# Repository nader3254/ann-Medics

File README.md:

# Ann-Medics System

This repo is for university graduation project

## What is Ann-Medics ?

Ann-Medics is a enhanced Remote Medical Device that store the 
human vitalities and monitor it for doctors,nurses and other medical stuff ,
it also  management system that works to organize the doctors’ hours, especially the anesthesiologists, given that their number is few in the world. Instead of waiting for the anesthesiologist for the patient to prepare for anesthesia, he can do anything else until this humble system summons him and sends a message to the doctor, and thus we will be as much as possible to save the treating doctor’s time.
 
https://www.youtube.com/watch?v=FgDbxe8dL8w&ab_channel=naderhany

## General setup  
**Host machine:** Ubuntu 18.04.4 LTS or later   
**Target machine:** Raspberry Pi 3B  , AD8232 ecg module , Max30102 ,buzzer 

## Setting up the environment for Raspberry pi
---

1. Download the raspbian image and 
```
  sudo apt install rpi-imager
``` 
note:select any raspbian lite image because we don't 
need to have x11 or wayland gui 

2. install the package dependencies
```
 sudo apt-get install libboost-all-dev libudev-dev libinput-dev libts-dev libmtdev-dev libjpeg-dev libfontconfig1-dev libssl-dev libdbus-1-dev libglib2.0-dev libxkbcommon-dev libegl1-mesa-dev libgbm-dev libgles2-mesa-dev mesa-common-dev libasound2-dev libpulse-dev gstreamer1.0-omx libgstreamer1.0-dev libgstreamer-plugins-base1.0-dev  gstreamer1.0-alsa libvpx-dev libsrtp2-dev libsnappy-dev libnss3-dev "^libxcb.*" flex bison libxslt-dev ruby gperf libbz2-dev libcups2-dev libatkmm-1.6-dev libxi6 libxcomposite1 libfreetype6-dev libicu-dev libsqlite3-dev libxslt1-dev
``` 
``` 
 sudo apt-get install libavcodec-dev libavformat-dev libswscale-dev libx11-dev freetds-dev libsqlite3-dev libpq-dev libiodbc2-dev firebird-dev libgst-dev libxext-dev libxcb1 libxcb1-dev libx11-xcb1 libx11-xcb-dev libxcb-keysyms1 libxcb-keysyms1-dev libxcb-image0 libxcb-image0-dev libxcb-shm0 libxcb-shm0-dev libxcb-icccm4 libxcb-icccm4-dev libxcb-sync1 libxcb-sync-dev libxcb-render-util0 libxcb-render-util0-dev libxcb-xfixes0-dev libxrender-dev libxcb-shape0-dev libxcb-randr0-dev libxcb-glx0-dev libxi-dev libdrm-dev libxcb-xinerama0 libxcb-xinerama0-dev libatspi2.0-dev libxcursor-dev libxcomposite-dev libxdamage-dev libxss-dev libxtst-dev libpci-dev libcap-dev libxrandr-dev libdirectfb-dev libaudio-dev libxkbcommon-x11-dev

``` 
This will install a bunch of libraries from the Debian repository that Qt needed to deploy various kinds of applications on Raspberry Pi.

We also will make a directory that will hold the Qt installation targeting Raspberry Pi, as specified in the previous section. Actually, this can be done at every time before sending Qt 6 build from host machine to the Raspberry Pi, but in this guide we will create it now:
```
 sudo mkdir /usr/local/qt6
```
this is all for raspberry pi

## Setting up the environment for HOST Machine 
---

1. Install Cross Compiler
```
sudo apt install gcc-aarch64-linux-gnu g++-aarch64-linux-gnu
```
2. Setting up SSH Connection

We also want to setup an SSH connection between Raspberry Pi and a host machine. This is needed to transfer data between both devices. The official Raspberry Pi documentation page provided a very detailed and thorough instruction on how to setup SSH between Raspberry Pi and other device, so you can refer this step into that https://www.raspberrypi.com/documentation/computers/remote-access.html#ssh.

3. Building Sysroot from Device

We need to build a Sysroot from our own Raspberry Pi device in the host machine. To do this, we will copy and paste a few directories from Raspberry Pi using rsync through SSH. If rsync is not installed yet in your host machine, simply install it by executing sudo apt install rsync.

After the host machine and Raspberry Pi is connected,
```
 rsync -avz --rsync-path="sudo rsync" --delete <pi_username>@<pi_ip_address>:/lib rpi-sysroot
 rsync -avz --rsync-path="sudo rsync" --delete <pi_username>@<pi_ip_address>:/usr/include rpi-sysroot/usr
 rsync -avz --rsync-path="sudo rsync" --delete <pi_username>@<pi_ip_address>:/usr/lib rpi-sysroot/usr
 rsync -avz --rsync-path="sudo rsync" --delete <pi_username>@<pi_ip_address>:/opt/vc rpi-sysroot/opt
```
Change <pi_username> and <pi_ip_address> with your Raspberry Pi username and IP Address, respectively.

Note: Your Raspberry Pi might not have a directory named /opt/vc, and it is fine. Usually this directory contains proprietary Broadcom libraries, but during the testing the author did not find any issue with the lack of this directory.

After building our own sysroot, we need to fix absolute symbolic links that were broken during the syncing process by converting them to relative symlinks. The easiest, fastest way to do this is to use a command-line tool called symlinks, which is available from the Ubuntu official repository.
```
 sudo apt install symlinks
 cd ~
 symlinks -rc rpi-sysroot
```

---
1. downloading qt source codes 
```
cd $HOME
git clone "https://codereview.qt-project.org/qt/qt5"
cd qt5/
git checkout 6.4.0
perl init-repository -f
cd ..
mkdir $HOME/qt-hostbuild
cd $HOME/qt-hostbuild/
cmake ../qt5/ -GNinja -DCMAKE_BUILD_TYPE=Release -DQT_BUILD_EXAMPLES=OFF -DQT_BUILD_TESTS=OFF -DCMAKE_INSTALL_PREFIX=$HOME/qt-host
cmake --build . --parallel 8
cmake --install .
```

2. Create a Toolchain File

First, we want to create our own CMake toolchain file. This file is important to link the right compilers and libraries so that CMake can produces the suitable Qt build for Raspberry Pi. For this guide, we will use the following CMake code and save it as toolchain.cmake.
```
cmake_minimum_required(VERSION 3.18)
include_guard(GLOBAL)

set(CMAKE_SYSTEM_NAME Linux)
set(CMAKE_SYSTEM_PROCESSOR arm)

set(TARGET_SYSROOT /path/to/your/sysroot)
set(CMAKE_SYSROOT ${TARGET_SYSROOT})

set(ENV{PKG_CONFIG_PATH} $PKG_CONFIG_PATH:/usr/lib/aarch64-linux-gnu/pkgconfig)
set(ENV{PKG_CONFIG_LIBDIR} /usr/lib/pkgconfig:/usr/share/pkgconfig/:${TARGET_SYSROOT}/usr/lib/aarch64-linux-gnu/pkgconfig:${TARGET_SYSROOT}/usr/lib/pkgconfig)
set(ENV{PKG_CONFIG_SYSROOT_DIR} ${CMAKE_SYSROOT})

# if you use other version of gcc and g++ than gcc/g++ 9, you must change the following variables
set(CMAKE_C_COMPILER /usr/bin/aarch64-linux-gnu-gcc-9)
set(CMAKE_CXX_COMPILER /usr/bin/aarch64-linux-gnu-g++-9)

set(CMAKE_C_FLAGS "${CMAKE_C_FLAGS} -I${TARGET_SYSROOT}/usr/include")
set(CMAKE_CXX_FLAGS "${CMAKE_C_FLAGS}")

set(QT_COMPILER_FLAGS "-march=armv8-a")
set(QT_COMPILER_FLAGS_RELEASE "-O2 -pipe")
set(QT_LINKER_FLAGS "-Wl,-O1 -Wl,--hash-style=gnu -Wl,--as-needed")

set(CMAKE_FIND_ROOT_PATH_MODE_PROGRAM NEVER)
set(CMAKE_FIND_ROOT_PATH_MODE_LIBRARY ONLY)
set(CMAKE_FIND_ROOT_PATH_MODE_INCLUDE ONLY)
set(CMAKE_FIND_ROOT_PATH_MODE_PACKAGE ONLY)
set(CMAKE_INSTALL_RPATH_USE_LINK_PATH TRUE)
set(CMAKE_BUILD_RPATH ${TARGET_SYSROOT})

include(CMakeInitializeConfigs)

function(cmake_initialize_per_config_variable _PREFIX _DOCSTRING)
  if (_PREFIX MATCHES "CMAKE_(C|CXX|ASM)_FLAGS")
    set(CMAKE_${CMAKE_MATCH_1}_FLAGS_INIT "${QT_COMPILER_FLAGS}")
        
    foreach (config DEBUG RELEASE MINSIZEREL RELWITHDEBINFO)
      if (DEFINED QT_COMPILER_FLAGS_${config})
        set(CMAKE_${CMAKE_MATCH_1}_FLAGS_${config}_INIT "${QT_COMPILER_FLAGS_${config}}")
      endif()
    endforeach()
  endif()

  if (_PREFIX MATCHES "CMAKE_(SHARED|MODULE|EXE)_LINKER_FLAGS")
    foreach (config SHARED MODULE EXE)
      set(CMAKE_${config}_LINKER_FLAGS_INIT "${QT_LINKER_FLAGS}")
    endforeach()
  endif()

  _cmake_initialize_per_config_variable(${ARGV})
endfunction()

set(XCB_PATH_VARIABLE ${TARGET_SYSROOT})

set(GL_INC_DIR ${TARGET_SYSROOT}/usr/include)
set(GL_LIB_DIR ${TARGET_SYSROOT}:${TARGET_SYSROOT}/usr/lib/aarch64-linux-gnu/:${TARGET_SYSROOT}/usr:${TARGET_SYSROOT}/usr/lib)

set(EGL_INCLUDE_DIR ${GL_INC_DIR})
set(EGL_LIBRARY ${XCB_PATH_VARIABLE}/usr/lib/aarch64-linux-gnu/libEGL.so)

set(OPENGL_INCLUDE_DIR ${GL_INC_DIR})
set(OPENGL_opengl_LIBRARY ${XCB_PATH_VARIABLE}/usr/lib/aarch64-linux-gnu/libOpenGL.so)

set(GLESv2_INCLUDE_DIR ${GL_INC_DIR})
set(GLIB_LIBRARY ${XCB_PATH_VARIABLE}/usr/lib/aarch64-linux-gnu/libGLESv2.so)

set(GLESv2_INCLUDE_DIR ${GL_INC_DIR})
set(GLESv2_LIBRARY ${XCB_PATH_VARIABLE}/usr/lib/aarch64-linux-gnu/libGLESv2.so)

set(gbm_INCLUDE_DIR ${GL_INC_DIR})
set(gbm_LIBRARY ${XCB_PATH_VARIABLE}/usr/lib/aarch64-linux-gnu/libgbm.so)

set(Libdrm_INCLUDE_DIR ${GL_INC_DIR})
set(Libdrm_LIBRARY ${XCB_PATH_VARIABLE}/usr/lib/aarch64-linux-gnu/libdrm.so)

set(XCB_XCB_INCLUDE_DIR ${GL_INC_DIR})
set(XCB_XCB_LIBRARY ${XCB_PATH_VARIABLE}/usr/lib/aarch64-linux-gnu/libxcb.so)
```
Now that we have our toolchain, as well as the cross compiler and sysroot, we can continue with configuring and building Qt for our Raspberry Pi!

As decided in the planning process, we will put all build configuration files on qtpi-build, so let's cd into that directory:
```
 cd ~/qtpi-build
```
Now inside this directory, we can run this configuration command:
```
 ../qt5/configure -release -opengl es2 -nomake examples -nomake tests -qt-host-path $HOME/qt-host -extprefix $HOME/qt-raspi -prefix /usr/local/qt6 -device linux-rasp-pi4-aarch64 -device-option CROSS_COMPILE=aarch64-linux-gnu- -- -DCMAKE_TOOLCHAIN_FILE=$HOME/toolchain.cmake -DQT_FEATURE_xcb=ON -DFEATURE_xcb_xlib=ON -DQT_FEATURE_xlib=ON
The command above will run a configuration script that came with the Qt source code and complementing it with the CMake toolchain that we just created. It is equivalent to this CMake command:
```
```
 cmake ../qt5/ -GNinja -DCMAKE_BUILD_TYPE=Release -DINPUT_opengl=es2 -DQT_BUILD_EXAMPLES=OFF -DQT_BUILD_TESTS=OFF -DQT_HOST_PATH=$HOME/qt-host -DCMAKE_STAGING_PREFIX=$HOME/qt-raspi -DCMAKE_INSTALL_PREFIX=/usr/local/qt6 -DCMAKE_TOOLCHAIN_FILE=$HOME/toolchain.cmake -DQT_QMAKE_TARGET_MKSPEC=devices/linux-rasp-pi4-aarch64 -DQT_FEATURE_xcb=ON -DFEATURE_xcb_xlib=ON -DQT_FEATURE_xlib=ON
```
Note: Both commands will do exactly the same thing: configuring Qt to be installed in folder qt-raspi on the host machine, with expectation that it will populate usr/local/qt6 on the Raspberry Pi. If you already run the first command, then there is no need to run the second command.

The Qt installation from this build will be suitable to run Qt ARM64 applications using X11 as the windowing system. You can check this page from Qt Docs to learn more about xcb plugins.

In more advanced cases, check this page from Qt Documentation if you want to use other windowing systems such as Wayland or EGLFS.

We can then proceed with building and installing.
```
 cmake --build . --parallel 4
 cmake --install .
```
After Qt is successfully installed on ~/qt-raspi, we will then send this Qt installation back to the Raspberry Pi.

To do this, we can use rsync as we did when building sysroot, or scp. Both will accomplish the same thing, and there should be no significant difference between both of them.

To use rsync:
```
rsync -avz --rsync-path="sudo rsync" /path/to/qt-raspi/* <pi_username>@<pi_ip_address>:/usr/local/qt6
```
To use scp:
```
 cd ~/qt-raspi
 scp -r * <pi_username>@<pi_ip_address>:/usr/local/qt6
```

3. Final Configuration on Raspberry Pi
To ensure our Qt 5 installation can be run on Raspberry Pi, we need to setup a few environment variables. All of this can be done on the host device via SSH.
```
ssh pi@169.254.187.77
```
## enter your raspberry pi user password, if prompted
```
 export LD_LIBRARY_PATH=$LD_LIBRARY_PATH:/usr/local/qt6/lib/
```

4. Compiling and Running Qt Project
```
 cd ~/qt5/qtbase/examples/gui/analogclock/
 ls ## make sure there is a CMakeLists.txt file
 ~/qt-raspi/bin/qt-cmake CMakeLists.txt
```
### CMake is configuring here. After it is done without any error, we can proceed to build and install it
```
 cmake --build . --parallel 4
 cmake --install .
```
We now have the binary of our application ready to be run on the Raspberry Pi. We can then send the binary to our Raspberry Pi using either scp or rsync and run the application (either through SSH or directly on the Raspberry Pi with keyboard and mouse connected).
```
 scp -r gui_analogclock <pi_username>@<pi_ip_address>:/home/pi
 ssh <pi_username>@<pi_ip_address>
 cd ~ ## or cd to the directory where you send the binary
 ./gui_analogclock
```

now you are ready download our repo and go to device directory and build it
for your device .

# References 

1. [Qt Documentation](https://doc.qt.io/qt-5/index.html)  
2. [Using Qt Creator to cross-compile and debug Raspberry Pi Qt5 apps ](https://jumpnowtek.com/rpi/Qt-Creator-Setup-for-RPi-cross-development.html) 
3. [Qt C++ GUI Tutorial for Beginners](https://www.youtube.com/playlist?list=PLS1QulWo1RIZiBcTr5urECberTITj7gjA)  
4. [Intel Edison audio output to Bluetooth speaker](https://tl00.wordpress.com/2015/01/28/11/)

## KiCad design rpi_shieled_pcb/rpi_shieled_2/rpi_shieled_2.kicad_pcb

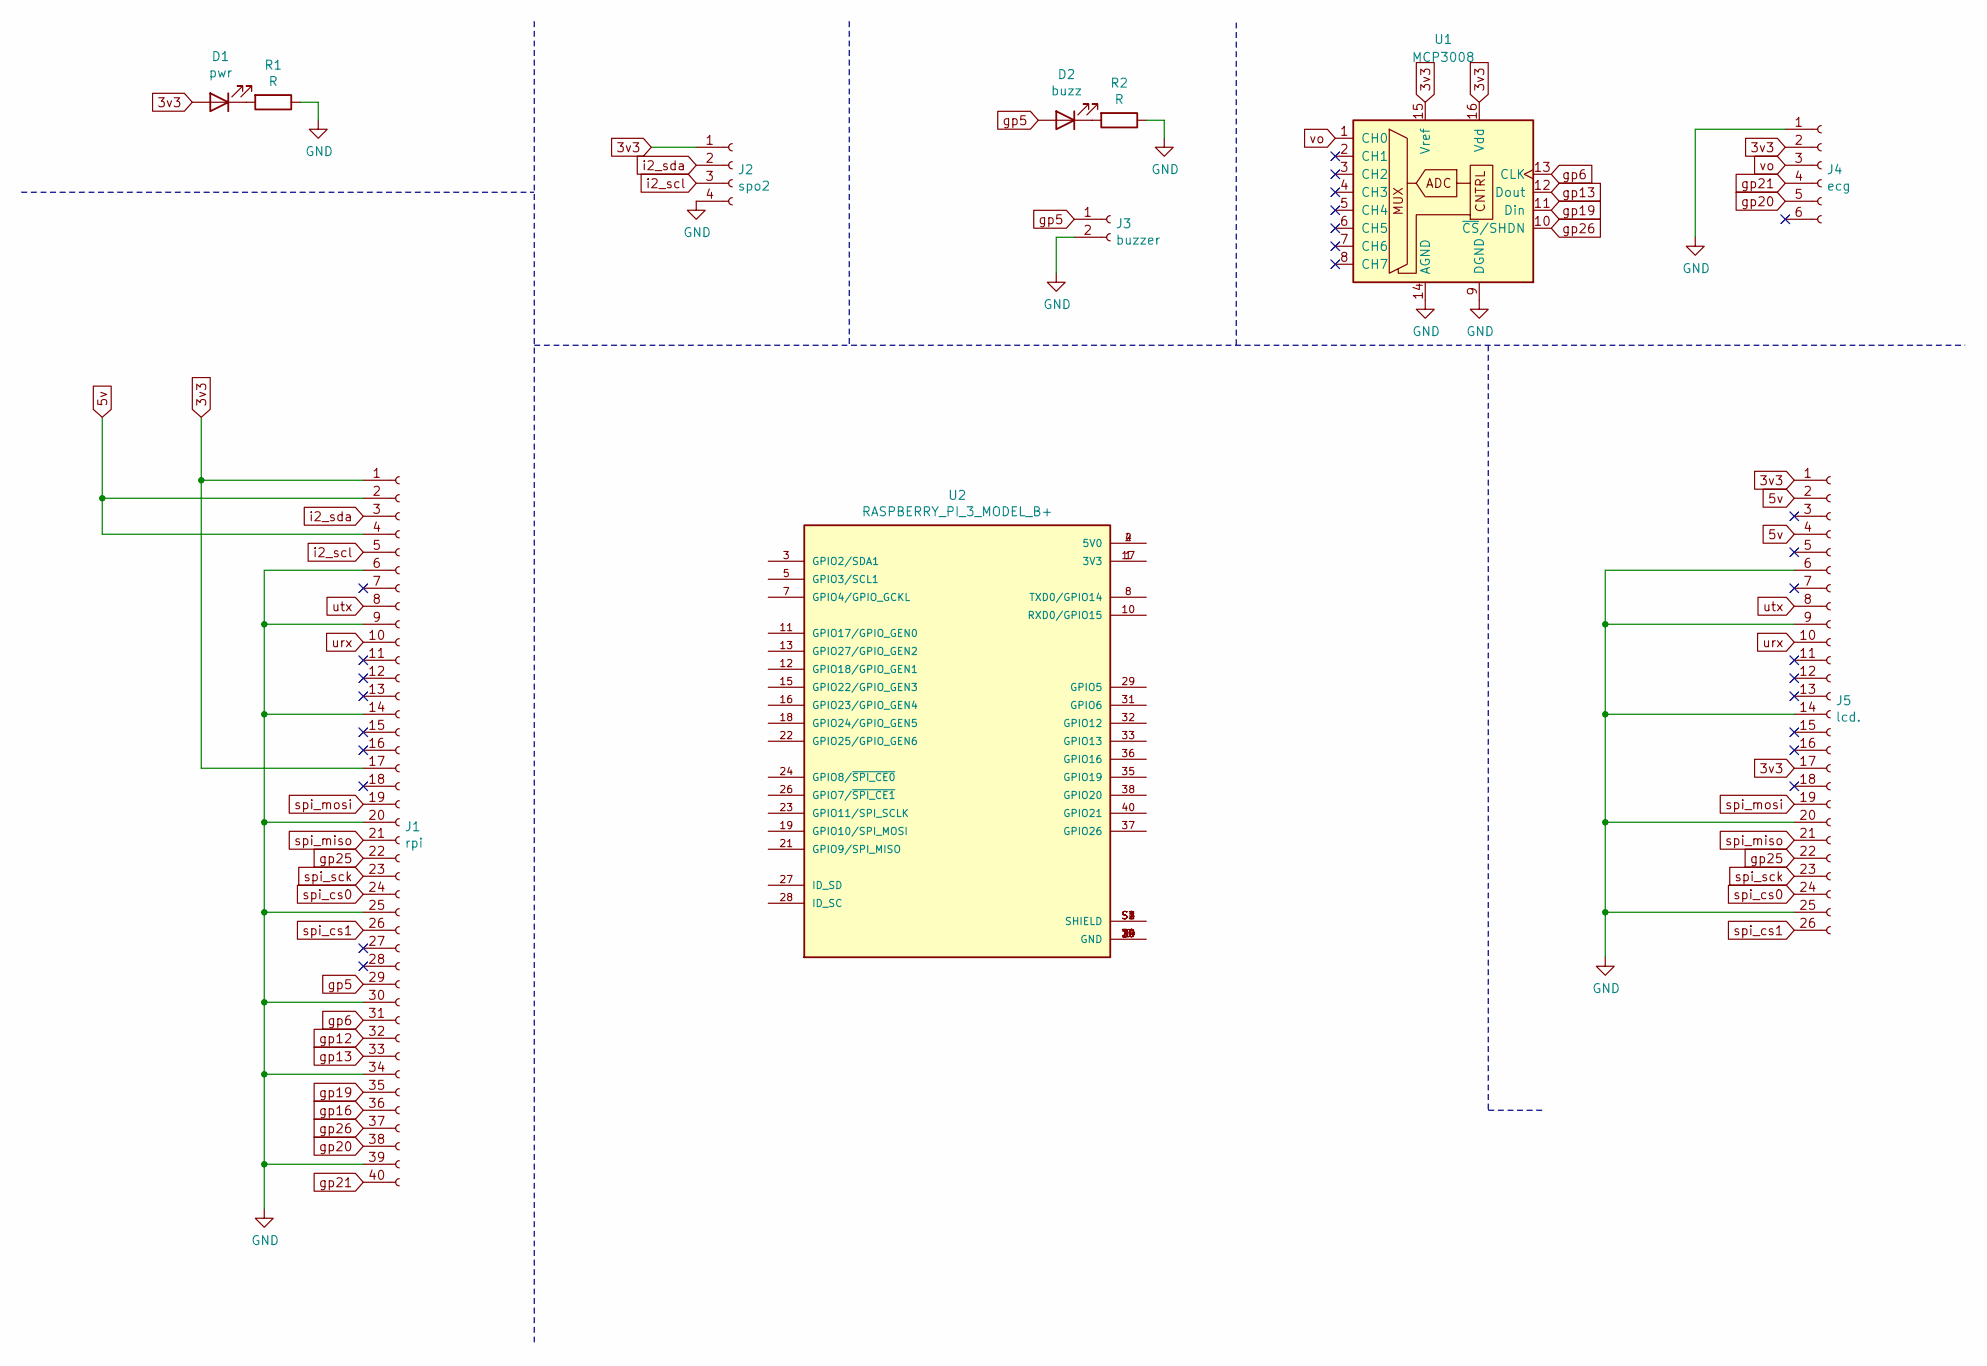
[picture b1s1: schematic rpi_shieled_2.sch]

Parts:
D1: pwr; LED_D2.0mm_W4.8mm_H2.5mm_FlatTop
D2: buzz; LED_D2.0mm_W4.8mm_H2.5mm_FlatTop
J1: rpi; PinSocket_2x20_P2.54mm_Vertical
J2: spo2; PinSocket_1x04_P2.54mm_Vertical
J3: buzzer; PinSocket_1x02_P2.54mm_Vertical
J4: ecg; PinSocket_1x06_P2.54mm_Vertical
J5: lcd.; PinSocket_2x13_P2.54mm_Vertical
R1, R2: R; R_Axial_DIN0204_L3.6mm_D1.6mm_P5.08mm_Vertical
U1: MCP3008; DIP-12_W10.16mm
U2: RASPBERRY_PI_3_MODEL_B+; MODULE_RASPBERRY_PI_3_MODEL_B+; PARTREV 1.0

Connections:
3v3: D1.2 (A), J1.1, J1.17, J2.1, J4.2, J5.1, J5.17, U1.15 (Vref), U1.16 (Vdd)
5v: J1.2, J1.4, J5.2, J5.4
GND: J1.6, J1.9, J1.14, J1.20, J1.25, J1.30, J1.34, J1.39, J2.4, J3.2, J4.1, J5.6, J5.9, J5.14, J5.20, J5.25, R1.1, R2.1, U1.9 (DGND), U1.14 (AGND)
unnamed: D1.1 (K), R1.2
unnamed: D2.1 (K), R2.2
unnamed: U2.1 (3V3), U2.17 (3V3)
unnamed: U2.2 (5V0), U2.4 (5V0)
unnamed: U2.6 (GND), U2.9 (GND), U2.14 (GND), U2.20 (GND), U2.25 (GND), U2.30 (GND), U2.34 (GND), U2.39 (GND)
unnamed: U2.S1 (SHIELD), U2.S2 (SHIELD), U2.S3 (SHIELD), U2.S4 (SHIELD)
gp5: D2.2 (A), J1.29, J3.1
gp6: J1.31, U1.13 (CLK)
gp12: J1.32
gp13: J1.33, U1.12 (Dout)
gp16: J1.36
gp19: J1.35, U1.11 (Din)
gp20: J1.38, J4.5
gp21: J1.40, J4.4
gp25: J1.22, J5.22
gp26: J1.37, U1.10 (~CS~/SHDN)
i2_scl: J1.5, J2.3
i2_sda: J1.3, J2.2
spi_cs0: J1.24, J5.24
spi_cs1: J1.26, J5.26
spi_miso: J1.21, J5.21
spi_mosi: J1.19, J5.19
spi_sck: J1.23, J5.23
urx: J1.10, J5.10
utx: J1.8, J5.8
vo: J4.3, U1.1 (CH0)

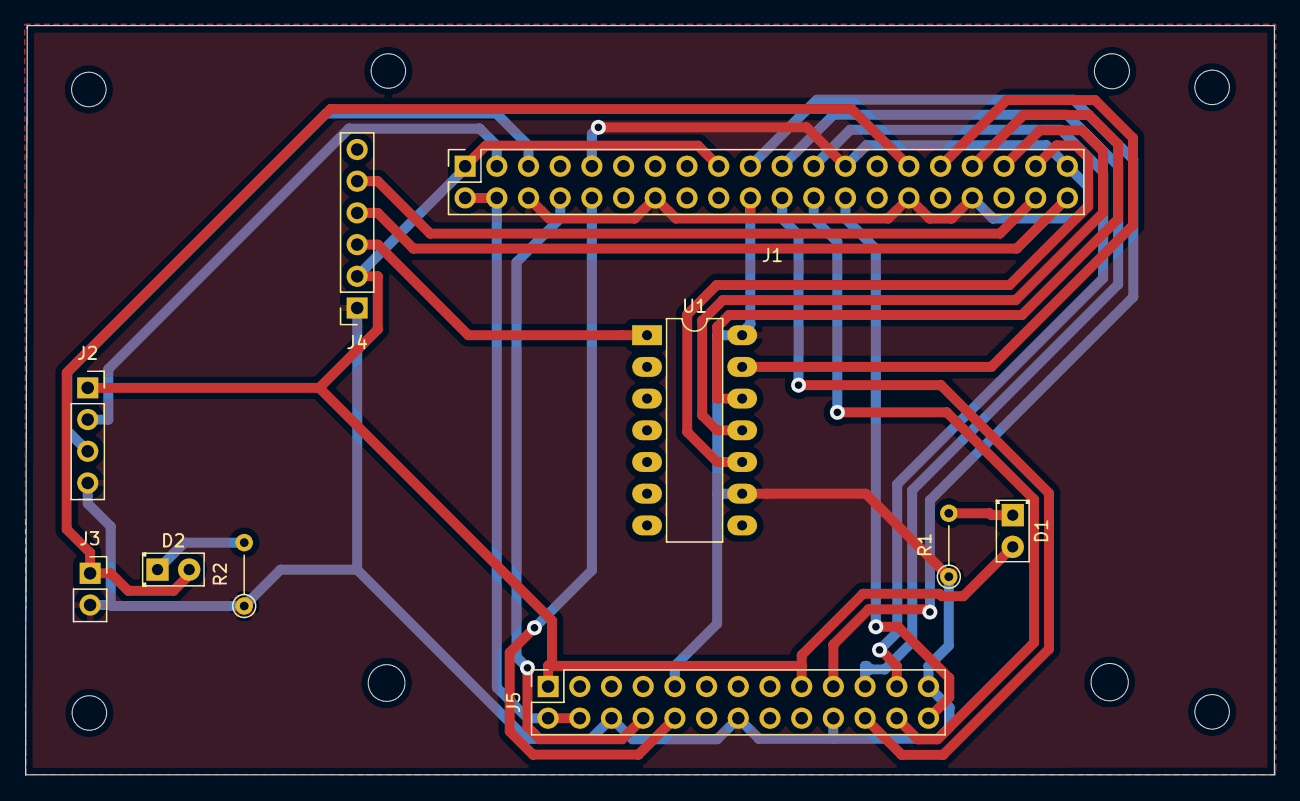
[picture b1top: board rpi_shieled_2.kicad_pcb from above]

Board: 2 copper layers, 100.1 x 60.1 mm, 10 parts (0 on the bottom side), 23 nets.

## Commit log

2022-12-16 second commit
2022-12-16 third commit
2023-01-07 fourth commit
2023-02-01 ecg_spo2_buzzer
2023-02-01 ecg_spo2_buzzer3
2023-02-01 ecg_spo2_buzzer4
2023-02-01 ecg_spo2_buzzer5
2023-02-01 ecg_spo2_buzzer6
2023-02-16 pcb commit
